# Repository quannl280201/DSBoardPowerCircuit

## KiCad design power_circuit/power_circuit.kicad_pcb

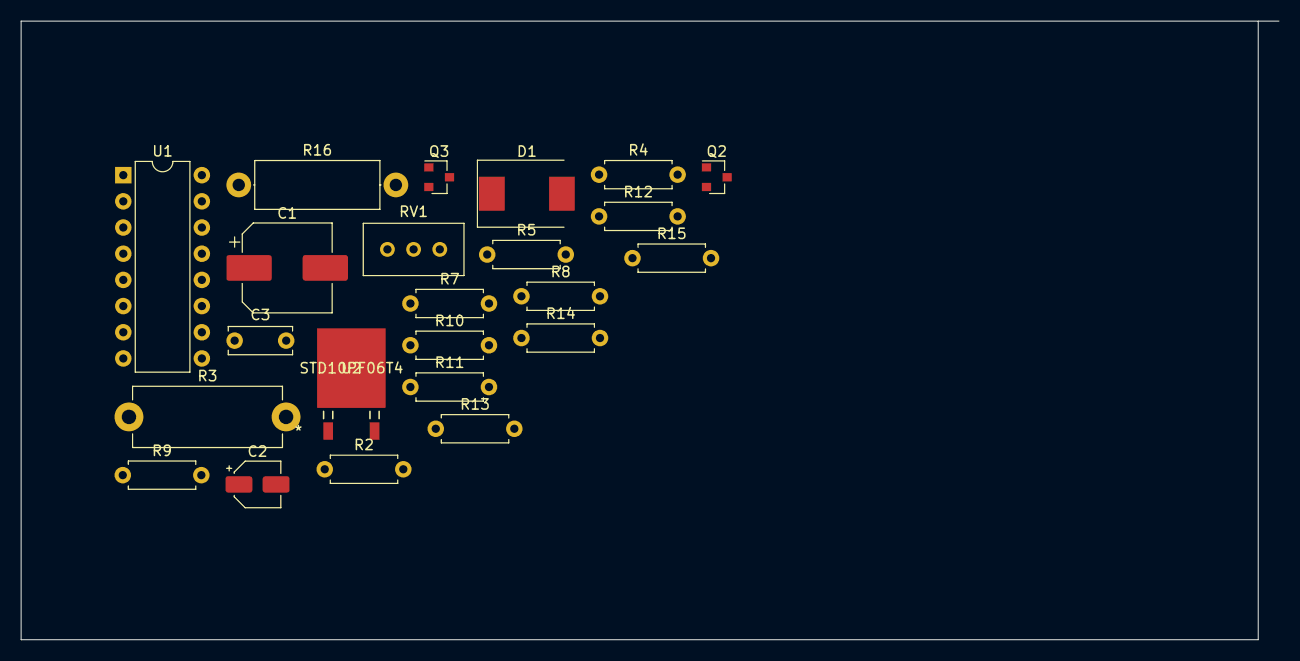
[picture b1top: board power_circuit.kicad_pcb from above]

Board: 2 copper layers, 122.0 x 60.0 mm, 23 parts (0 on the bottom side), 18 nets, no tracks yet.

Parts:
C1: 100u; CP_Elec_8x10.5
C2: 2.5u; CP_Elec_4x5.4
C3: 0.001u; C_Disc_D6.0mm_W2.5mm_P5.00mm
D1: SS34; D_SMC
Q2: BC817; SOT-23
Q3: BC807; SOT-23
R2, R10, R11: 4.7k; R_Axial_DIN0207_L6.3mm_D2.5mm_P7.62mm_Horizontal
R3: 0.22; R_Axial_DIN0614_L14.3mm_D5.7mm_P15.24mm_Horizontal
R4: 1.5k; R_Axial_DIN0207_L6.3mm_D2.5mm_P7.62mm_Horizontal
R5: 100; R_Axial_DIN0207_L6.3mm_D2.5mm_P7.62mm_Horizontal
R7: 470; R_Axial_DIN0207_L6.3mm_D2.5mm_P7.62mm_Horizontal
R8, R15: 47k; R_Axial_DIN0207_L6.3mm_D2.5mm_P7.62mm_Horizontal
R9: 5.6k; R_Axial_DIN0207_L6.3mm_D2.5mm_P7.62mm_Horizontal
R12, R14: 1k; R_Axial_DIN0207_L6.3mm_D2.5mm_P7.62mm_Horizontal
R13: 10k; R_Axial_DIN0207_L6.3mm_D2.5mm_P7.62mm_Horizontal
R16: 22; R_Axial_DIN0414_L11.9mm_D4.5mm_P15.24mm_Horizontal
RV1: 5k; Potentiometer_Bourns_3296W_Vertical
U1: TL494; DIP-16_W7.62mm
U2: STD10PF06T4

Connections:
+24V: R4.1, R5.1, U1.12, U2.3
/REF: C2.1, R9.2, R10.2, R13.2, U1.14
/Vg: R16.1, U2.1
/Vout+: C1.1, RV1.1
/Vout-: R3.2, U1.16
GND: C1.2, C3.1, D1.2, Q3.3, R2.2, R3.1, R11.2, R12.2, R14.2, R15.2, U1.7, U1.9, U1.10, U1.13
unnamed: C2.2, R13.1, R14.1, U1.4
unnamed: C3.2, U1.5
unnamed: D1.1, U2.2
unnamed: Q2.1, Q3.1, R4.2, U1.8, U1.11
unnamed: Q2.2, Q3.2, R16.2
unnamed: Q2.3, R5.2
unnamed: R2.1, RV1.2, U1.1
unnamed: R7.1, R8.2, U1.2
unnamed: R8.1, U1.3
unnamed: R7.2, R10.1, R11.1
unnamed: R9.1, R12.1, U1.15
unnamed: R15.1, U1.6

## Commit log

2021-04-27 Initialize repository

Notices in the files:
parts and their libraries:
Copyright 2016 Accelerated Designs. All rights reserved.
